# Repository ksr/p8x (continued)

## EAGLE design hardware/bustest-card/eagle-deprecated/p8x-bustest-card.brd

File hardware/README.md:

# hardware/

The physical machine: one passive backplane, six plug-in CPU cards, a PS/2 input
card, and a bus test card for bring-up. Each board has its own directory holding a
chip-by-chip README, a theory of operation or design doc, and the **KiCad** board
(`kicad/`: the `.kicad_pcb`, the Freerouting session, orderable Gerbers, a
placement PDF and renders). Every board is designed and routed; none has been
fabricated yet. Board status: **[KICAD-BOARDS.md](KICAD-BOARDS.md)**; build
readiness against the emulator and the FPGA: **[RECONCILIATION.md](RECONCILIATION.md)**.

| Board | Directory | Function |
|-------|-----------|----------|
| Control / Microcode | [control-card/](control-card/README.md) | Clock, reset, sequencer, microcode EPROMs, IR, condition mux, front panel |
| Register Bank | [regbank-card/](regbank-card/README.md) | P0–P3 16-bit pointer registers, address-bus drivers |
| ALU | [alu-card/](alu-card/README.md) | A/B/T/T2 registers, 74181 ALU, shifter, FLAGS |
| Memory | [memory-card/](memory-card/README.md) | 28C256 ROM (6 KB window, `$0000–$17FF`) + 2× 62256 SRAM, address decode (rev F) |
| I/O | [io-card/](io-card/README.md) | Switches, LEDs, bus monitor, two 6850 ACIAs (`$FF04/05`, `$FF08/09`) with two DB9s (rev B) |
| CF-IDE | [cf-card/](cf-card/README.md) | Two CompactFlash drives in 8-bit True IDE mode: `$FF10–$FF17` and `$FF18–$FF1F` (rev B) |
| PS/2 | [ps2-card/](ps2-card/README.md) | Keyboard + mouse at `$FF58–$FF5F`: an ATmega1284P behind a latch bridge (rev A) |
| Bus test | [bustest-card/](bustest-card/p8x-bustest-card-design.md) | Bring-up tool: a Raspberry Pi Pico drives the bus over USB, one microcycle at a time |
| Backplane | [backplane/](backplane/p8x-backplane-design.md) | 8-slot passive 96-pin DIN 41612 bus (rev C2), 262 × 128 mm |

The plug-in cards are all 280 × 140 mm, 4-layer (signals on the outer layers, GND
and +5 V planes inside).

**Eagle (frozen).** The first board generation was drawn in Eagle/Fusion from
`generators/gen_eagle.py`. On 2026-09-18 the KiCad flow replaced it: each board's
Eagle `.sch`/`.brd` and its schematic and placement PDFs moved to
`<board>/eagle-deprecated/`, frozen at rev E, and are no longer maintained (the
Eagle memory card still carries the old 8 KB ROM decode; the KiCad rev F board has
the 6 KB one). `gen_eagle.py` stays the source of the netlists.

> **Deprecated:** the standalone **LED test card** (a write-only 8-LED output
> latch that decoded `$FF0C`) was a CAD-workflow trial, never built. It has been
> moved to [`deprecated/led-card/`](deprecated/led-card/) and its I/O address
> `$FF0C` is now free. (This is unrelated to the `$FF02` LED latch the emulator
> traces, which stays.) The combined I/O + CF + PS/2 **peripheral card** is parked
> in `parked/peripheral-card/` (2026-09-19); the design went back to three cards.

### Not yet realised as TTL boards
See **[RECONCILIATION.md](RECONCILIATION.md)** for the full board-vs-emulator/FPGA
build-readiness pass. Subsystems the emulator and/or the FPGA already provide that
have **no TTL card** yet:

| Subsystem | Where it lives now | TTL board |
|-----------|--------------------|-----------|
| MDU multiply/divide (`$FF30–$FF3F`) | emulator model + FPGA (`mdu_core.v`) | none yet |
| Graphics-language port (`$FF50–$FF54`) | emulator model + the Tang Nano 20K graphics card | none (the FPGA card *is* the graphics engine) |
| IRQ controller (`$FF06` device-IRQ model) | emulator model | none yet — the next card to design |

**[assembly/](assembly/README.md)** — 3D renders of the assembled machine: the
backplane with all eight cards standing in their slots, each card populated
(rendered from the boards by `generators/render_assembly.py`; slot order inside).

`p8x-bom.csv` — the orderable bill of materials for the whole machine
(ICs, sockets, connectors, passives), generated by
[`../generators/gen_bom.py`](../generators/).

## Rebuilding boards

**Generators are canon** — never hand-edit a `.kicad_pcb`. The netlists live in
[`../generators/gen_eagle.py`](../generators/) (`CARDS`, `busnet()`);
`gen_kicad.py` turns a card into a placed KiCad board (the memory, I/O, CF, PS/2
cards and the backplane have bespoke placement scripts in their `kicad/`
directories), Freerouting routes it, and `check_card.sh` runs the readiness check
(ERC, gate-level simulation where a testbench exists, DRC, mounting-hole keepout,
fab minimums). One command does all of it, from the repository root:

```sh
sh generators/build.sh memory-card      # one board (or: all)
sh generators/check_card.sh memory-card # the readiness check alone
```

It needs KiCad 10 and a Freerouting jar. See
[../generators/README.md](../generators/README.md) for the scripts and
[../docs/p8x-card-standards.md](../docs/p8x-card-standards.md) for the rules
every card follows.

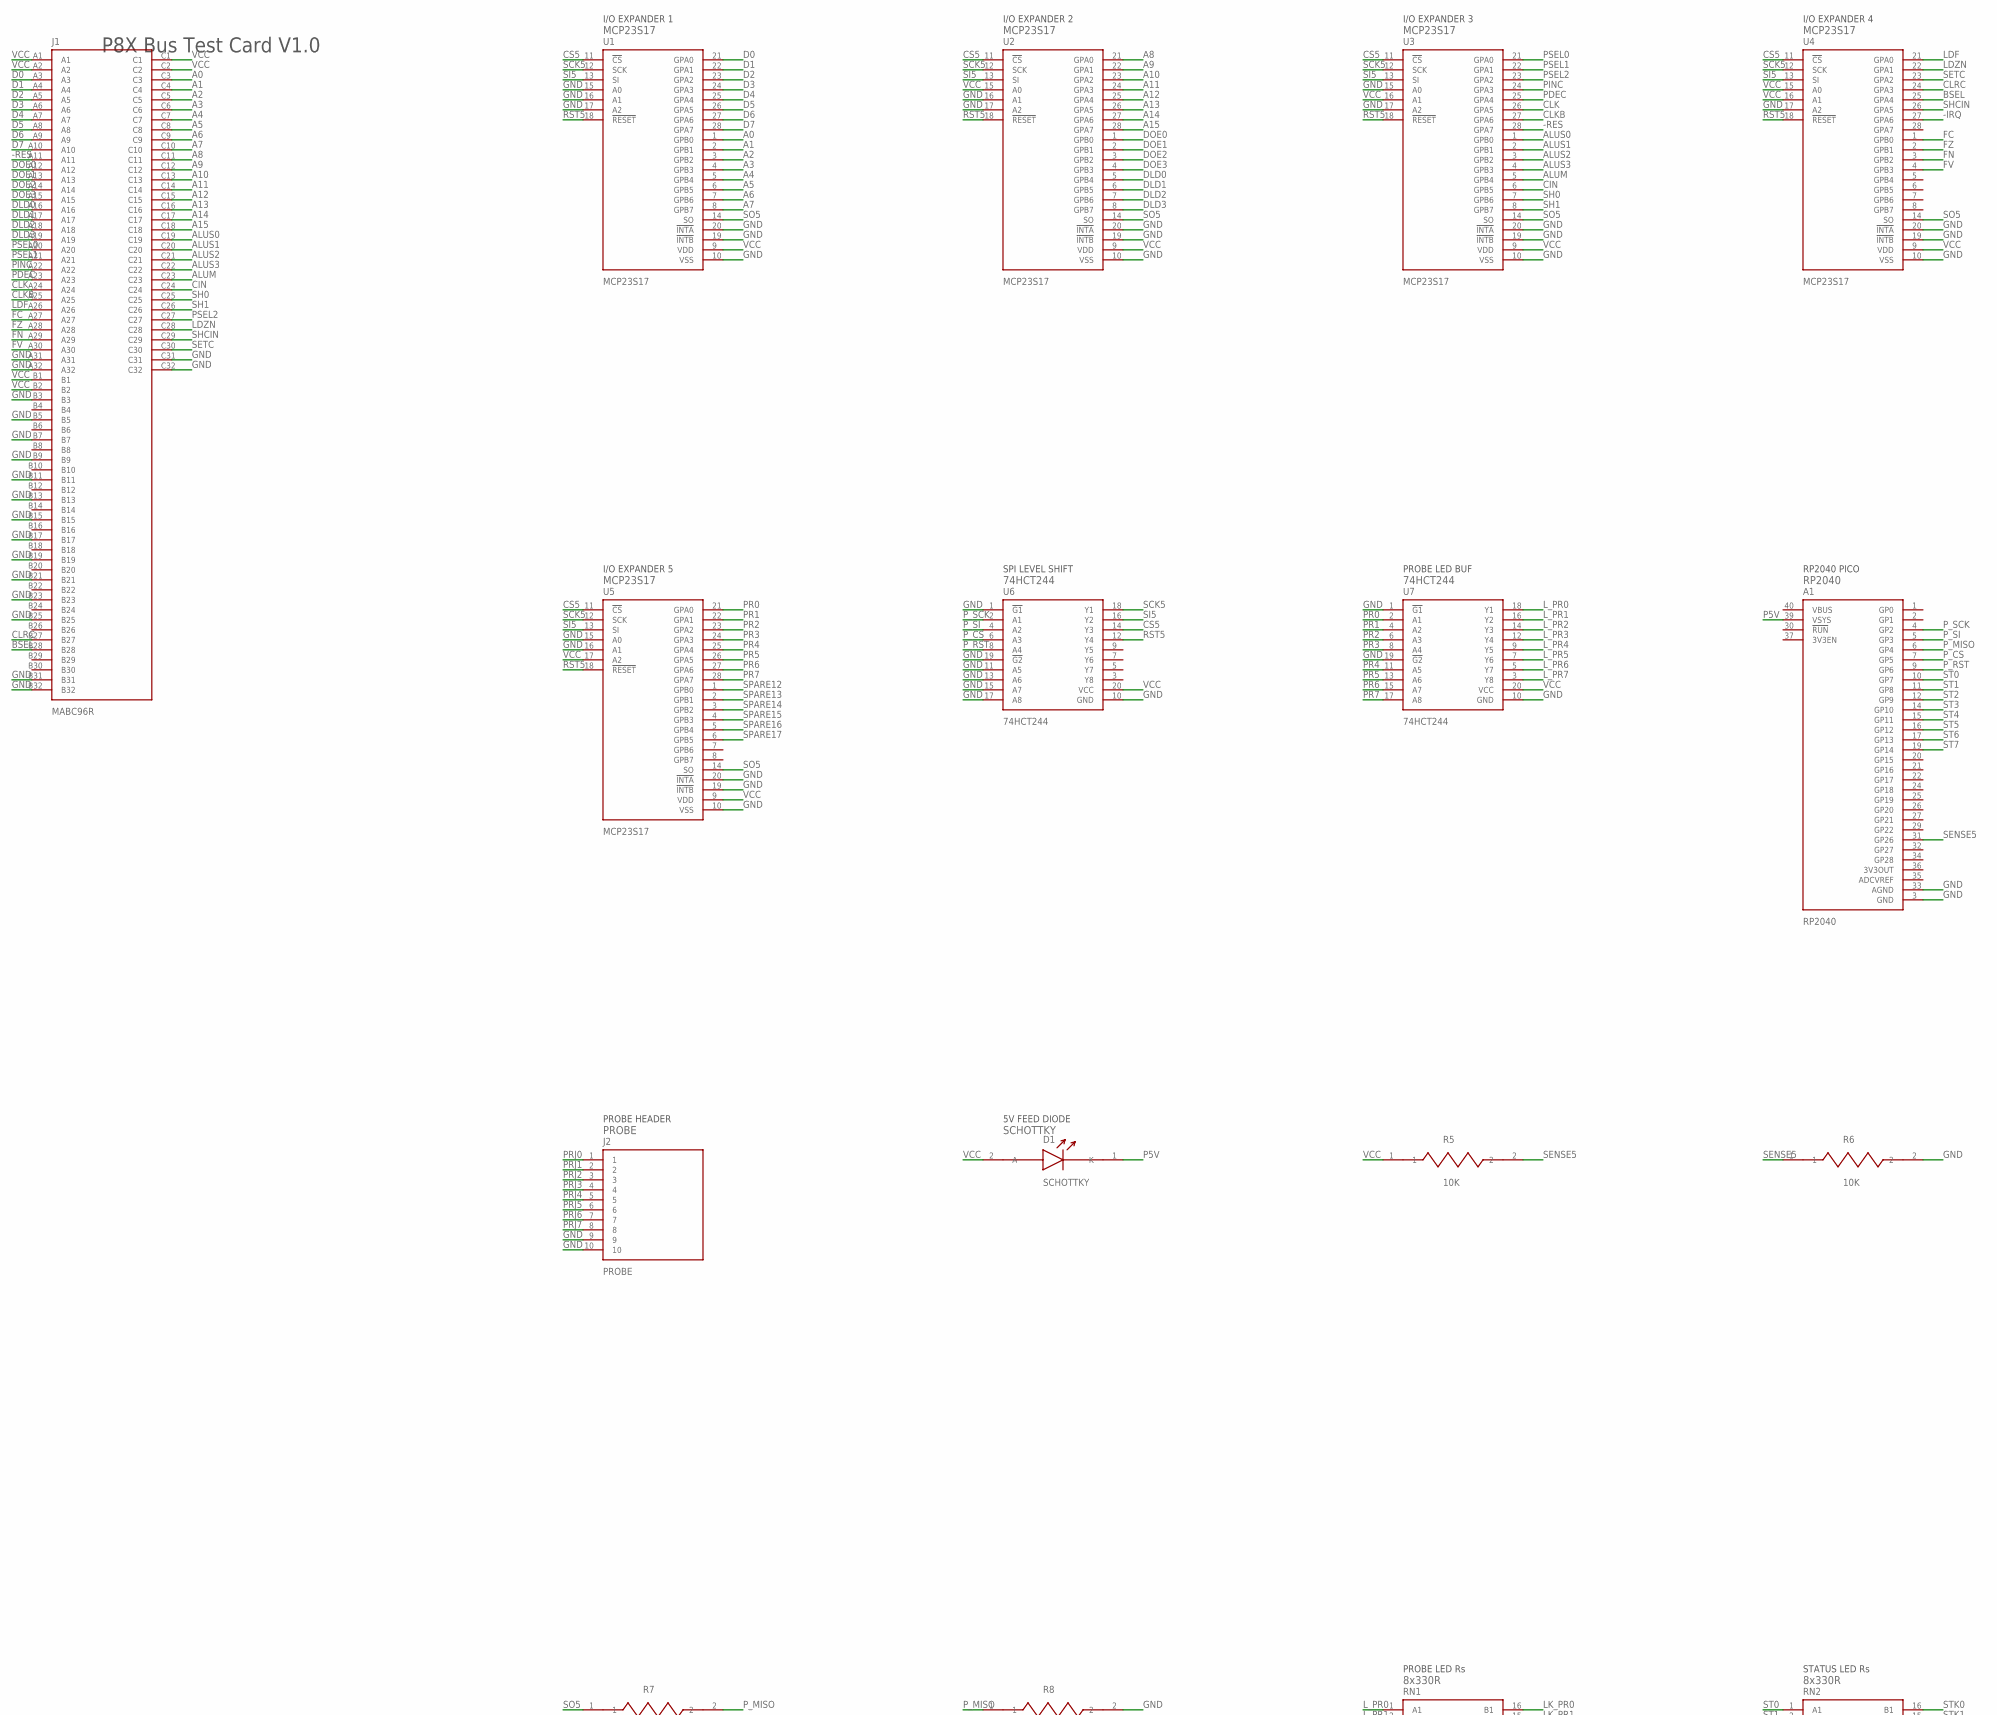
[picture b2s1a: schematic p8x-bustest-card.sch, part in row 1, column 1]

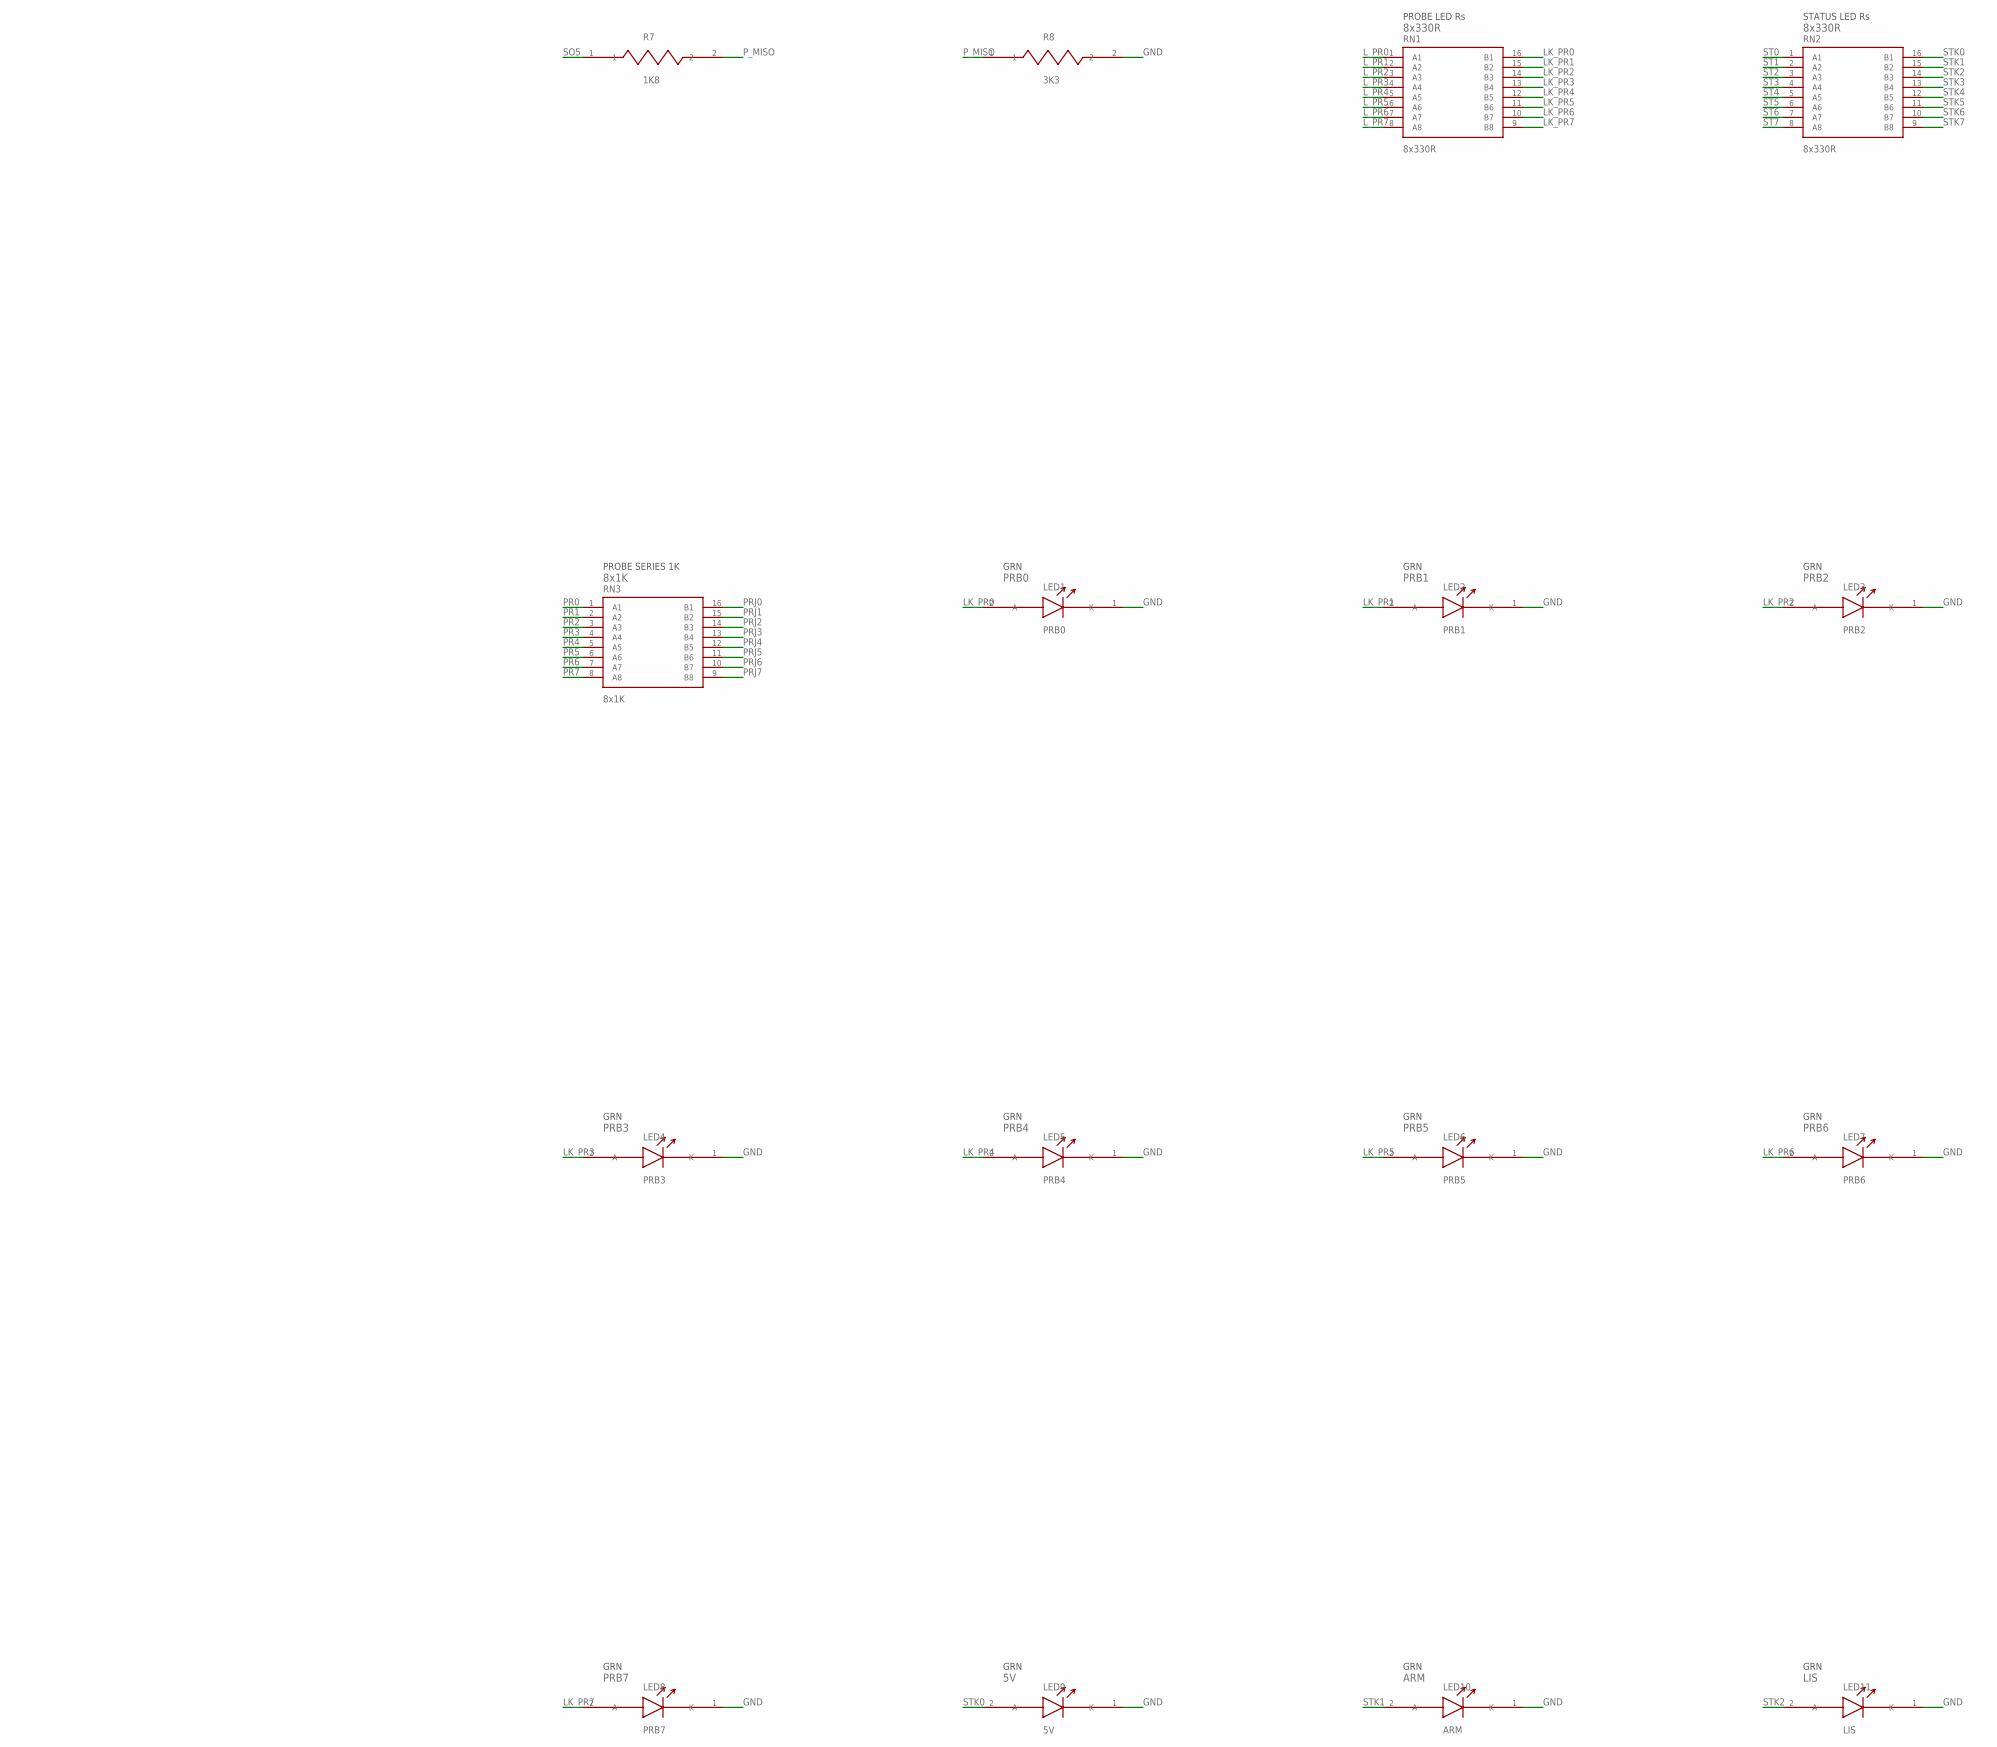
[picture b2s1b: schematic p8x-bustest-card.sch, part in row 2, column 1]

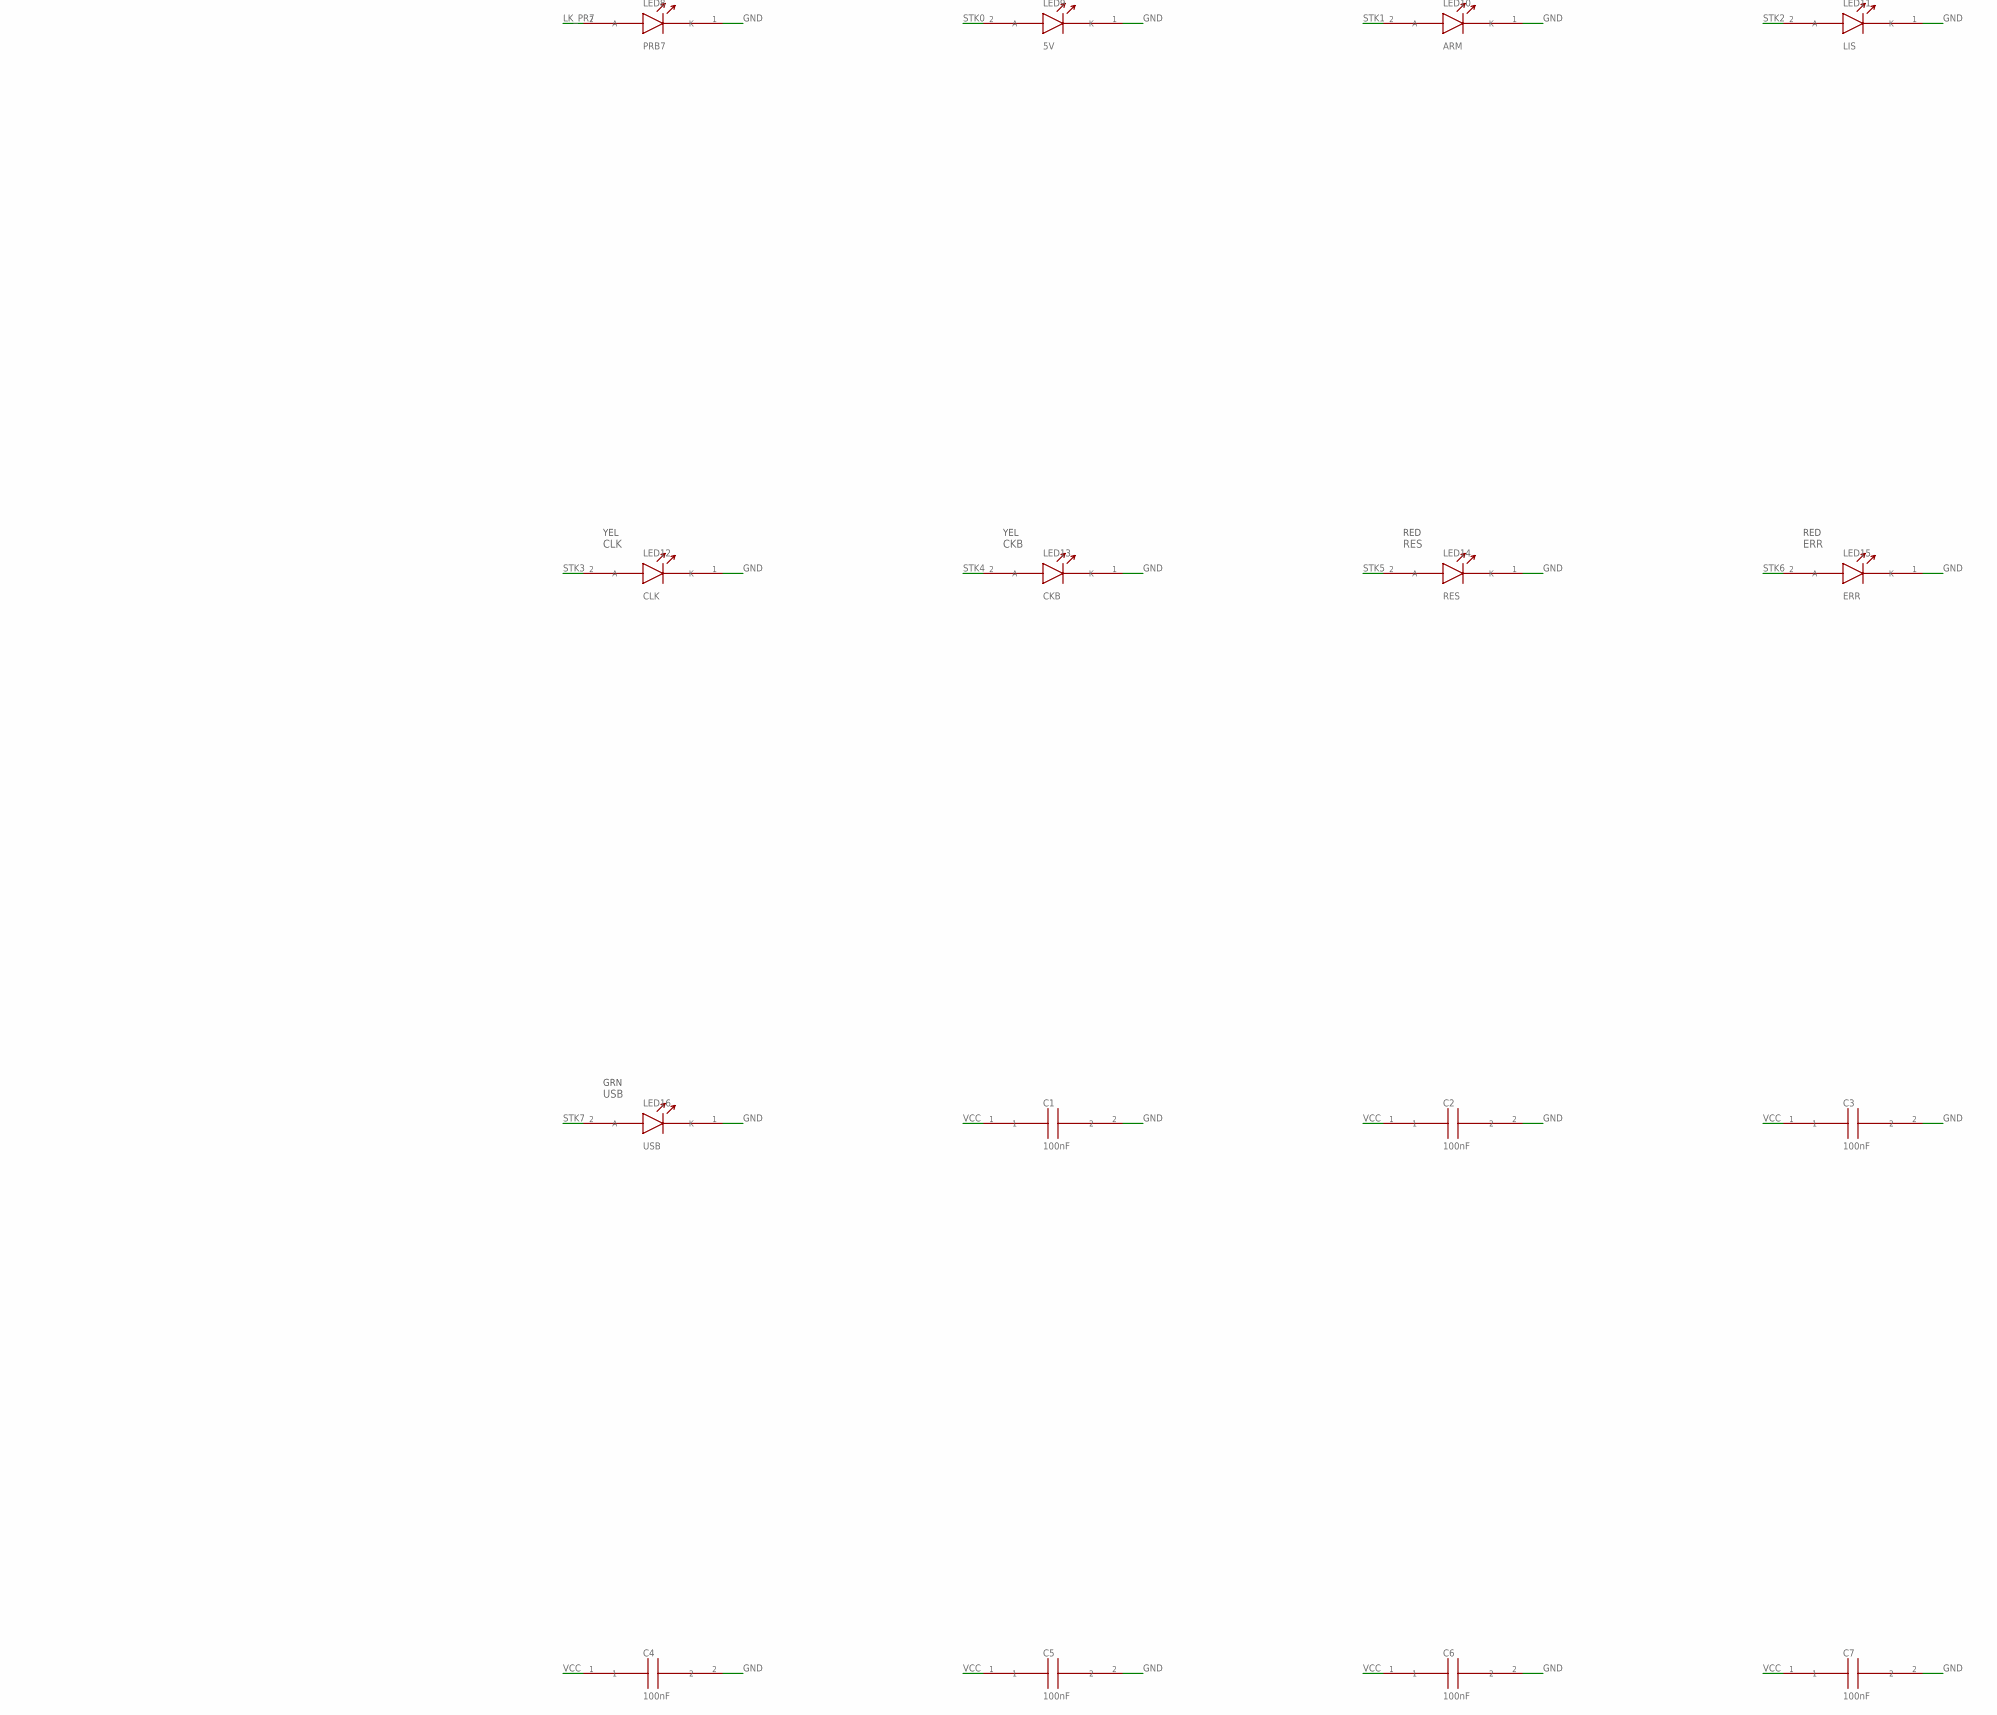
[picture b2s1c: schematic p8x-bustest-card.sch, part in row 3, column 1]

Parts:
A1: RP2040; PICO40
C1, C2, C3, C4, C5, C6, C7: 100nF; C_DISC1
D1: SCHOTTKY; LED5
J1: MABC96R
J2: PROBE; HDR10
LED1: PRB0; LED5
LED2: PRB1; LED5
LED3: PRB2; LED5
LED4: PRB3; LED5
LED5: PRB4; LED5
LED6: PRB5; LED5
LED7: PRB6; LED5
LED8: PRB7; LED5
LED9: 5V; LED5
LED10: ARM; LED5
LED11: LIS; LED5
LED12: CLK; LED5
LED13: CKB; LED5
LED14: RES; LED5
LED15: ERR; LED5
LED16: USB; LED5
R5, R6: 10K; R_AXIAL
R7: 1K8; R_AXIAL
R8: 3K3; R_AXIAL
RN1, RN2: 8x330R; DIP16
RN3: 8x1K; DIP16
U1, U2, U3, U4, U5: MCP23S17; DIP28N
U6, U7: 74HCT244; DIP20

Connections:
-IRQ: U4.27 (GPA6)
-RES: J1.A11, U3.28 (GPA7)
A0: J1.C3, U1.1 (GPB0)
A1: J1.C4, U1.2 (GPB1)
A2: J1.C5, U1.3 (GPB2)
A3: J1.C6, U1.4 (GPB3)
A4: J1.C7, U1.5 (GPB4)
A5: J1.C8, U1.6 (GPB5)
A6: J1.C9, U1.7 (GPB6)
A7: J1.C10, U1.8 (GPB7)
A8: J1.C11, U2.21 (GPA0)
A9: J1.C12, U2.22 (GPA1)
A10: J1.C13, U2.23 (GPA2)
A11: J1.C14, U2.24 (GPA3)
A12: J1.C15, U2.25 (GPA4)
A13: J1.C16, U2.26 (GPA5)
A14: J1.C17, U2.27 (GPA6)
A15: J1.C18, U2.28 (GPA7)
ALUM: J1.C23, U3.5 (GPB4)
ALUS0: J1.C19, U3.1 (GPB0)
ALUS1: J1.C20, U3.2 (GPB1)
ALUS2: J1.C21, U3.3 (GPB2)
ALUS3: J1.C22, U3.4 (GPB3)
BSEL: J1.B28, U4.25 (GPA4)
CIN: J1.C24, U3.6 (GPB5)
CLK: J1.A24, U3.26 (GPA5)
CLKB: J1.A25, U3.27 (GPA6)
CLRC: J1.B27, U4.24 (GPA3)
CS5: U1.11 (!CS), U2.11 (!CS), U3.11 (!CS), U4.11 (!CS), U5.11 (!CS), U6.14 (Y3)
D0: J1.A3, U1.21 (GPA0)
D1: J1.A4, U1.22 (GPA1)
D2: J1.A5, U1.23 (GPA2)
D3: J1.A6, U1.24 (GPA3)
D4: J1.A7, U1.25 (GPA4)
D5: J1.A8, U1.26 (GPA5)
D6: J1.A9, U1.27 (GPA6)
D7: J1.A10, U1.28 (GPA7)
DLD0: J1.A16, U2.5 (GPB4)
DLD1: J1.A17, U2.6 (GPB5)
DLD2: J1.A18, U2.7 (GPB6)
DLD3: J1.A19, U2.8 (GPB7)
DOE0: J1.A12, U2.1 (GPB0)
DOE1: J1.A13, U2.2 (GPB1)
DOE2: J1.A14, U2.3 (GPB2)
DOE3: J1.A15, U2.4 (GPB3)
FC: J1.A27, U4.1 (GPB0)
FN: J1.A29, U4.3 (GPB2)
FV: J1.A30, U4.4 (GPB3)
FZ: J1.A28, U4.2 (GPB1)
GND: A1.3 (GND), A1.33 (AGND), C1.2, C2.2, C3.2, C4.2, C5.2, C6.2, C7.2, J1.A31, J1.A32, J1.B3, J1.B5, J1.B7, J1.B9, J1.B11, J1.B13, J1.B15, J1.B17, J1.B19, J1.B21, J1.B23, J1.B25, J1.B31, J1.B32, J1.C31, J1.C32, J2.9, J2.10, LED1.1 (K), LED2.1 (K), LED3.1 (K), LED4.1 (K), LED5.1 (K), LED6.1 (K), LED7.1 (K), LED8.1 (K), LED9.1 (K), LED10.1 (K), LED11.1 (K), LED12.1 (K), LED13.1 (K), LED14.1 (K), LED15.1 (K), LED16.1 (K), R6.2, R8.2, U1.10 (VSS), U1.15 (A0), U1.16 (A1), U1.17 (A2), U1.19 (!INTB), U1.20 (!INTA), U2.10 (VSS), U2.16 (A1), U2.17 (A2), U2.19 (!INTB), U2.20 (!INTA), U3.10 (VSS), U3.15 (A0), U3.17 (A2), U3.19 (!INTB), U3.20 (!INTA), U4.10 (VSS), U4.17 (A2), U4.19 (!INTB), U4.20 (!INTA), U5.10 (VSS), U5.15 (A0), U5.16 (A1), U5.19 (!INTB), U5.20 (!INTA), U6.1 (!G1), U6.10 (GND), U6.11 (A5), U6.13 (A6), U6.15 (A7), U6.17 (A8), U6.19 (!G2), U7.1 (!G1), U7.10 (GND), U7.19 (!G2)
LDF: J1.A26, U4.21 (GPA0)
LDZN: J1.C28, U4.22 (GPA1)
LK_PR0: LED1.2 (A), RN1.16 (B1)
LK_PR1: LED2.2 (A), RN1.15 (B2)
LK_PR2: LED3.2 (A), RN1.14 (B3)
LK_PR3: LED4.2 (A), RN1.13 (B4)
LK_PR4: LED5.2 (A), RN1.12 (B5)
LK_PR5: LED6.2 (A), RN1.11 (B6)
LK_PR6: LED7.2 (A), RN1.10 (B7)
LK_PR7: LED8.2 (A), RN1.9 (B8)
L_PR0: RN1.1 (A1), U7.18 (Y1)
L_PR1: RN1.2 (A2), U7.16 (Y2)
L_PR2: RN1.3 (A3), U7.14 (Y3)
L_PR3: RN1.4 (A4), U7.12 (Y4)
L_PR4: RN1.5 (A5), U7.9 (Y5)
L_PR5: RN1.6 (A6), U7.7 (Y6)
L_PR6: RN1.7 (A7), U7.5 (Y7)
L_PR7: RN1.8 (A8), U7.3 (Y8)
P5V: A1.39 (VSYS), D1.1 (K)
PDEC: J1.A23, U3.25 (GPA4)
PINC: J1.A22, U3.24 (GPA3)
PR0: RN3.1 (A1), U5.21 (GPA0), U7.2 (A1)
PR1: RN3.2 (A2), U5.22 (GPA1), U7.4 (A2)
PR2: RN3.3 (A3), U5.23 (GPA2), U7.6 (A3)
PR3: RN3.4 (A4), U5.24 (GPA3), U7.8 (A4)
PR4: RN3.5 (A5), U5.25 (GPA4), U7.11 (A5)
PR5: RN3.6 (A6), U5.26 (GPA5), U7.13 (A6)
PR6: RN3.7 (A7), U5.27 (GPA6), U7.15 (A7)
PR7: RN3.8 (A8), U5.28 (GPA7), U7.17 (A8)
PRJ0: J2.1, RN3.16 (B1)
PRJ1: J2.2, RN3.15 (B2)
PRJ2: J2.3, RN3.14 (B3)
PRJ3: J2.4, RN3.13 (B4)
PRJ4: J2.5, RN3.12 (B5)
PRJ5: J2.6, RN3.11 (B6)
PRJ6: J2.7, RN3.10 (B7)
PRJ7: J2.8, RN3.9 (B8)
PSEL0: J1.A20, U3.21 (GPA0)
PSEL1: J1.A21, U3.22 (GPA1)
PSEL2: J1.C27, U3.23 (GPA2)
P_CS: A1.7 (GP5), U6.6 (A3)
P_MISO: A1.6 (GP4), R7.2, R8.1
P_RST: A1.9 (GP6), U6.8 (A4)
P_SCK: A1.4 (GP2), U6.2 (A1)
P_SI: A1.5 (GP3), U6.4 (A2)
RST5: U1.18 (!RESET), U2.18 (!RESET), U3.18 (!RESET), U4.18 (!RESET), U5.18 (!RESET), U6.12 (Y4)
SCK5: U1.12 (SCK), U2.12 (SCK), U3.12 (SCK), U4.12 (SCK), U5.12 (SCK), U6.18 (Y1)
SENSE5: A1.31 (GP26), R5.2, R6.1
SETC: J1.C30, U4.23 (GPA2)
SH0: J1.C25, U3.7 (GPB6)
SH1: J1.C26, U3.8 (GPB7)
SHCIN: J1.C29, U4.26 (GPA5)
SI5: U1.13 (SI), U2.13 (SI), U3.13 (SI), U4.13 (SI), U5.13 (SI), U6.16 (Y2)
SO5: R7.1, U1.14 (SO), U2.14 (SO), U3.14 (SO), U4.14 (SO), U5.14 (SO)
SPARE12: U5.1 (GPB0)
SPARE13: U5.2 (GPB1)
SPARE14: U5.3 (GPB2)
SPARE15: U5.4 (GPB3)
SPARE16: U5.5 (GPB4)
SPARE17: U5.6 (GPB5)
ST0: A1.10 (GP7), RN2.1 (A1)
ST1: A1.11 (GP8), RN2.2 (A2)
ST2: A1.12 (GP9), RN2.3 (A3)
ST3: A1.14 (GP10), RN2.4 (A4)
ST4: A1.15 (GP11), RN2.5 (A5)
ST5: A1.16 (GP12), RN2.6 (A6)
ST6: A1.17 (GP13), RN2.7 (A7)
ST7: A1.19 (GP14), RN2.8 (A8)
STK0: LED9.2 (A), RN2.16 (B1)
STK1: LED10.2 (A), RN2.15 (B2)
STK2: LED11.2 (A), RN2.14 (B3)
STK3: LED12.2 (A), RN2.13 (B4)
STK4: LED13.2 (A), RN2.12 (B5)
STK5: LED14.2 (A), RN2.11 (B6)
STK6: LED15.2 (A), RN2.10 (B7)
STK7: LED16.2 (A), RN2.9 (B8)
VCC: C1.1, C2.1, C3.1, C4.1, C5.1, C6.1, C7.1, D1.2 (A), J1.A1, J1.A2, J1.B1, J1.B2, J1.C1, J1.C2, R5.1, U1.9 (VDD), U2.9 (VDD), U2.15 (A0), U3.9 (VDD), U3.16 (A1), U4.9 (VDD), U4.15 (A0), U4.16 (A1), U5.9 (VDD), U5.17 (A2), U6.20 (VCC), U7.20 (VCC)

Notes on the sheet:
P8X Bus Test Card V1.0
I/O EXPANDER 1
MCP23S17
I/O EXPANDER 2
I/O EXPANDER 3
I/O EXPANDER 4
I/O EXPANDER 5
SPI LEVEL SHIFT
74HCT244
PROBE LED BUF
RP2040 PICO
RP2040
PROBE HEADER
PROBE
5V FEED DIODE
SCHOTTKY
PROBE LED Rs
8x330R
STATUS LED Rs
PROBE SERIES 1K
8x1K
GRN
PRB0
PRB1
PRB2
PRB3
PRB4
PRB5
PRB6
PRB7
ARM
LIS
YEL
CLK
CKB
RED
RES
ERR
USB

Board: 4 copper layers, 41 parts (0 on the bottom side), 120 nets, no tracks yet.

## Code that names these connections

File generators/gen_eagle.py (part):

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        if n==11: return "-RES"
        if 12<=n<=15: return "DOE%d"%(n-12)
        if 16<=n<=19: return "DLD%d"%(n-16)
        return {20:"PSEL0",21:"PSEL1",22:"PINC",23:"PDEC",24:"CLK",25:"CLKB",26:"LDF",
                27:"FC",28:"FZ",29:"FN",30:"FV"}.get(n)
    if 3<=n<=18: return "A%d"%(n-3)
    if 19<=n<=22: return "ALUS%d"%(n-19)
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D("JMP2X3",[str(k) for k in range(1,7)],[],{str(k):str(k) for k in range(1,7)},"HDR2X3")    # RX/TX swap block
# ATmega328P (DIP-28 narrow): PS/2 signal processor. Standard AVR DIP pinout.
D("ATMEGA328",
  ["!RESET","PD0","PD1","PD2","PD3","PD4","PB6","PB7","PD5","PD6","PD7",
   "PB0","PB1","PB2","PB3","PB4","PB5","AREF","PC0","PC1","PC2","PC3","PC4","PC5"],
  ["VCC","AVCC","GND","GND2"],
  {"!RESET":"1","PD0":"2","PD1":"3","PD2":"4","PD3":"5","PD4":"6","VCC":"7","GND":"8",
   "PB6":"9","PB7":"10","PD5":"11","PD6":"12","PD7":"13","PB0":"14","PB1":"15","PB2":"16",
   "PB3":"17","PB4":"18","PB5":"19","AVCC":"20","AREF":"21","GND2":"22","PC0":"23","PC1":"24",
   "PC2":"25","PC3":"26","PC4":"27","PC5":"28"},"DIP28N")
# 74HC688 8-bit magnitude comparator -- the PS/2 window ($FF58-5F) address compare.
D("74688",["!G","P0","Q0","P1","Q1","P2","Q2","P3","Q3","Q4","P4","Q5","P5","Q6","P6","Q7","P7"],
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# ATmega1284P (PDIP-40, 0.6"): PS/2 signal processor. 32 GPIO (4 full ports) leaves
# ~12 spare after the bus bridge -- enough to drive the status LEDs straight off the
# MCU and leave room for host->device TX + an IRQ line (no 74123 one-shot needed).
# SPI/ICSP is on PB5(MOSI)/PB6(MISO)/PB7(SCK). Internal RC osc -> XTAL pins unused.
D("ATMEGA1284",
  ["PB0","PB1","PB2","PB3","PB4","PB5","PB6","PB7","!RESET","XTAL2","XTAL1",
   "PD0","PD1","PD2","PD3","PD4","PD5","PD6","PD7","PC0","PC1","PC2","PC3","PC4","PC5",
   "PC6","PC7","AREF","PA7","PA6","PA5","PA4","PA3","PA2","PA1","PA0"],
  ["VCC","GND","AVCC","GND2"],
  {"PB0":"1","PB1":"2","PB2":"3","PB3":"4","PB4":"5","PB5":"6","PB6":"7","PB7":"8",
   "!RESET":"9","VCC":"10","GND":"11","XTAL2":"12","XTAL1":"13","PD0":"14","PD1":"15",
   "PD2":"16","PD3":"17","PD4":"18","PD5":"19","PD6":"20","PD7":"21","PC0":"22","PC1":"23",
   "PC2":"24","PC3":"25","PC4":"26","PC5":"27","PC6":"28","PC7":"29","AVCC":"30","GND2":"31",
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 "R4":("RES","1K"),"LED4":("LED","RUN-GRN"),
 "R5":("RES","1K"),"LED5":("LED","HALT-RED")}
# JP1 clock select (2x3, 2026-10-24): one shunt across a row picks the clock --
# 1-2 = 4 MHz, 3-4 = 2 MHz, 5-6 = 1 MHz; the even pins are all CLKRAW
N(n,"OSCO",("X1","OUT"),("JP1","1"),("U1","CLK"))
N(n,"DIVQA",("U1","QA"),("JP1","3")); N(n,"DIVQB",("U1","QB"),("JP1","5"))
N(n,"CLKRAW",("JP1","2"),("JP1","4"),("JP1","6"),("U3","1CLK"),("U3","2CLK"),("U5","1A"))
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# rev B 32-bit control word -> pipeline latches U14..U17 (8 bits each).
# Word bit b is latch U[14 + b//8], output Q[(b%8)+1].
PIPE={14:["DOE0","DOE1","DOE2","DOE3","DLD0","DLD1","DLD2","DLD3"],
 15:["PSEL0","PSEL1","PSEL2","PINC","PDEC","ALUS0","ALUS1","ALUS2"],
 16:["ALUS3","ALUM","CIN","SH0","SH1","LDF","FCOND0","FCOND1"],
 17:["FCOND2","URST","HALT","LDZN","SHCIN","SETC","CLRC","BSEL"]}
for k,sigs in PIPE.items():
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N(n,"LEDRN",("R4","2"),("LED4","A")); N(n,"LEDHL",("R5","2"),("LED5","A"))
card("control-card","P8X CONTROL/MICROCODE CARD REV B",ic,sm,n,
 {"D%d"%i for i in range(8)}|{"DOE%d"%i for i in range(4)}|{"DLD%d"%i for i in range(4)}|
 {"PSEL0","PSEL1","PSEL2","PINC","PDEC","ALUS0","ALUS1","ALUS2","ALUS3","ALUM","CIN","SH0","SH1",
  "LDF","CLK","CLKB","-RES","FC","FZ","FN","FV","LDZN","SHCIN","SETC","CLRC","BSEL","IRQ"},
 labels={"U19":"N^V XOR"})

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N(n,"VCC",("U39","G1")); N(n,"GND",("U39","!G2B"))
N(n,"CNTN",("U34","1Y"),("U39","!G2A"))
for p in range(6): N(n,"-CNT%d"%p,("U39","Y%d"%p))
N(n,"PINC",("U34","1A")); N(n,"PDEC",("U34","1B"),("U35","1A"))
N(n,"UDB",("U35","1Y"))
N(n,"GND",*[("U34",p) for p in ("2A","2B","3A","3B","4A","4B")],
  *[("U35",p) for p in ("3A","4A","5A","6A")],
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N(n,"LEDRD",("R4","2"),("LED4","A")); N(n,"LEDLD",("R5","2"),("LED5","A"))
# PT (PSEL=4) and PT2 (PSEL=5) scratch pointers -- rev D. Both are now four
# 74169 counters each (identical structure to P0-P3, a carry chain on !RCO->!ENT)
# so the 16-bit ops can PINC them, loaded from D0-7 on -LDLp/-LDHp and driven
# onto the pointer bus PB via two 74244 select buffers gated by -SELp. Counter
# numbering: PT=U41-44, PT2=U45-48; select buffers PT=U49/50, PT2=U51/52.
for p in (4,5):
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card("regbank-card","P8X REGISTER BANK CARD REV D (P0=PC P3=SP, PT+PT2 scratch counters)",ic,sm,n,
 {"D%d"%i for i in range(8)}|{"A%d"%i for i in range(16)}|
 {"DLD%d"%i for i in range(4)}|{"DOE%d"%i for i in range(4)}|
 {"PSEL0","PSEL1","PSEL2","PINC","PDEC","CLK","-RES"})

# ===================== ALU CARD ===============================================
n={}
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N(n,"TXD",("U14","TXD"),("U8","T1IN"))
N(n,"RXD",("U14","RXD"),("U8","R1OUT"))
# ACIA1 RS-232 through the RX/TX swap jumper JP1 to DB9-A. Center pins 3/4 = the
# MAX232 side (SOUT/SIN); pins 1/6 = DB9.3 (TXD), pins 2/5 = DB9.2 (RXD). A pair of
# shunts selects straight-through (DTE) or crossed (null-modem).
N(n,"SOUT",("U8","T1OUT"),("JP1","3")); N(n,"SIN",("U8","R1IN"),("JP1","4"))
N(n,"S1TXD",("JP1","1"),("JP1","6"),("DB9A","3")); N(n,"S1RXD",("JP1","2"),("JP1","5"),("DB9A","2"))
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N(pcn,"-WR1",("U27","Y1"),("U24","PC4"))                 # PSAST write -> '328 sense
N(pcn,"-WR3",("U27","Y3"),("U24","PC5"))                 # PSBST write -> '328 sense
# read latches: D = '328 MB[0:7] bus, Q -> P8X D0-7, CLK from '328 load lines
_MB=["PB0","PB1","PB2","PB3","PB4","PB5","PD6","PD7"]
for b in range(8):
    N(pcn,"MB%d"%b,("U24",_MB[b]),
      ("U28","D%d"%(b+1)),("U29","D%d"%(b+1)),("U30","D%d"%(b+1)),("U31","D%d"%(b+1)))
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N(pcn,"VCC",("RN3","COM"))
N(pcn,"PS2CKA",("RN3","R1")); N(pcn,"PS2DA",("RN3","R2"))
N(pcn,"PS2CKB",("RN3","R3")); N(pcn,"PS2DB",("RN3","R4"))
# ICSP (AVR 2x3): 1 MISO(PB4/MB4) 2 VCC 3 SCK(PB5/MB5) 4 MOSI(PB3/MB3) 5 !RESET 6 GND
N(pcn,"MB4",("JICSP","1")); N(pcn,"VCC",("JICSP","2")); N(pcn,"MB5",("JICSP","3"))
N(pcn,"MB3",("JICSP","4")); N(pcn,"-RESET",("JICSP","5"),("U24","!RESET"),("RRST","1"))
N(pcn,"GND",("JICSP","6")); N(pcn,"VCC",("RRST","2"))
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N(n,"PS2CKB",("U13","PD3")); N(n,"PS2DB",("U13","PD5"))
N(n,"VCC",("U13","AVCC")); N(n,"GND",("U13","GND2"))
# status LEDs, driven straight off the MCU (no one-shot -- firmware stretches the
# blink): PB0 = keyboard-read activity, PB1 = mouse-read activity, PB2 = keystroke
# available (lit while a kbd byte waits). Plus a plain power LED on VCC.
N(n,"LKR",("U13","PB0"),("RKR","2")); N(n,"LKRA",("RKR","1"),("LEDKR","A")); N(n,"GND",("LEDKR","K"))
N(n,"LMR",("U13","PB1"),("RMR","2")); N(n,"LMRA",("RMR","1"),("LEDMR","A")); N(n,"GND",("LEDMR","K"))
N(n,"LKA",("U13","PB2"),("RKA","2")); N(n,"LKAA",("RKA","1"),("LEDKA","A")); N(n,"GND",("LEDKA","K"))
N(n,"VCC",("RPWR","2")); N(n,"LPWRA",("RPWR","1"),("LEDPWR","A")); N(n,"GND",("LEDPWR","K"))
# PS/2 sockets + 10k open-drain pull-ups (RN1)
N(n,"PS2CKA",("PS2A","5")); N(n,"PS2DA",("PS2A","1"))
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N(n,"PS2CKA",("RN1","R1")); N(n,"PS2DA",("RN1","R2"))
N(n,"PS2CKB",("RN1","R3")); N(n,"PS2DB",("RN1","R4"))
N(n,"GND",("PS2A","SH"),("PS2B","SH"))                 # metal shield tabs -> GND
# ICSP (AVR 2x3): 1 MISO(PB6) 2 VCC 3 SCK(PB7) 4 MOSI(PB5) 5 !RESET 6 GND. On the
# 1284P the SPI pins are dedicated (not shared with the MB data bus, which is on PA).
N(n,"MISO",("JICSP","1"),("U13","PB6")); N(n,"VCC",("JICSP","2")); N(n,"SCK",("JICSP","3"),("U13","PB7"))
N(n,"MOSI",("JICSP","4"),("U13","PB5")); N(n,"-RESET",("JICSP","5"),("U13","!RESET"),("RRST","1"),("RRB","2"))
N(n,"GND",("JICSP","6")); N(n,"VCC",("RRST","2"))
# Bus reset -> '328 reset, through a 470R series isolation resistor (RRB). A system
# -RES (push-pull driven by the control card) pulls -RESET below the AVR threshold
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    if 8<=i<=14: pins.append(("U4","ABCDEFG"[i-8]))
    if i==13: pins.append(("U8","4A"))                             # rev E: A13 -> Q=OR(A13,A14) (ROM 8K decode)
    if i==14: pins.append(("U8","4B"))                             # A14 -> Q=OR(A13,A14)
    if i==15: pins+=[("U4","H"),("U7","1A"),("U11","1B"),("U7","2A"),("U7","2B")]  # A15 -> ROM8CE OR + -RAMCE/A15N
    mnet("A%d"%i,*pins)
mnet("-IOPG",("U4","Y"),("U7","1B"))
mnet("-RAMCE",("U7","1Y"),("U2","!CE"))
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N(n,"LEDWR",("R4","2"),("LED4","A"))
card("led-card","P8X LED OUTPUT CARD (DEPRECATED - test card, $FF0C now free)",ic,sm,n,
 {"D%d"%i for i in range(8)}|{"A1","A2","A3","A4"}|{"A%d"%i for i in range(8,16)}|
 {"DLD%d"%i for i in range(4)}|{"CLKB"},labels=led_labels,emit_files=False)  # DEPRECATED: emits no files

# ===================== BUS TEST CARD (USB-driven bring-up) ====================
# See hardware/bustest-card/p8x-bustest-card-design.md. A Pico drives 5 MCP23S17
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_map("U1","GPB",["A%d"%i for i in range(8)])
_map("U2","GPA",["A%d"%i for i in range(8,16)])
_map("U2","GPB",["DOE0","DOE1","DOE2","DOE3","DLD0","DLD1","DLD2","DLD3"])
_map("U3","GPA",["PSEL0","PSEL1","PSEL2","PINC","PDEC","CLK","CLKB","-RES"])
_map("U3","GPB",["ALUS0","ALUS1","ALUS2","ALUS3","ALUM","CIN","SH0","SH1"])
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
